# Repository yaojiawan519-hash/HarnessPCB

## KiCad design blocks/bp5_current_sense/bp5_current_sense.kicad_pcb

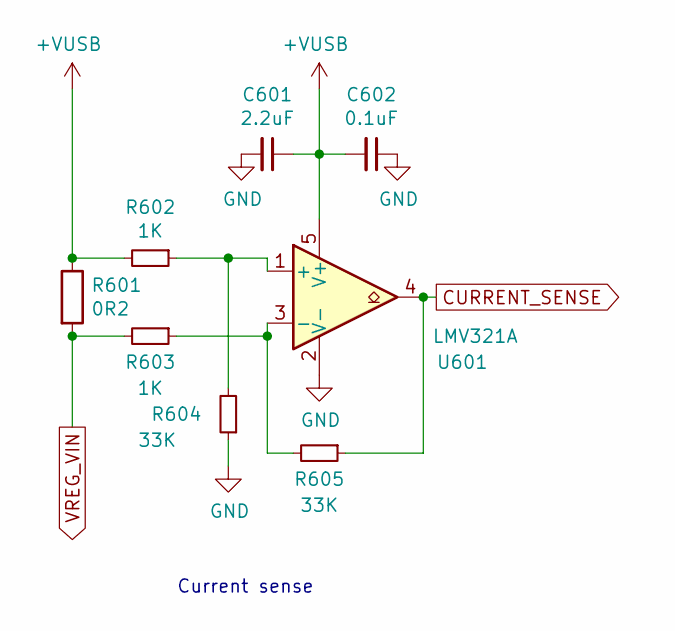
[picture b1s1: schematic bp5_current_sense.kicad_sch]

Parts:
C601: 2.2uF; C_0402_1005Metric
C602: 0.1uF; C_0402_1005Metric
R601: 0R2; R_2512_6332Metric_Pad1.40x3.35mm_HandSolder
R602, R603: 1K; R_0402_1005Metric
R604, R605: 33K; R_0402_1005Metric
U601: LMV321A; SOT-23-5

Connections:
+VUSB: C601.1, C602.2, R601.1, R602.2, U601.5 (V+)
CURRENT_SENSE: R605.1, U601.4
GND: C601.2, C602.1, R604.1, U601.2 (V-)
unnamed: R602.1, R604.2, U601.1 (+)
unnamed: R603.1, R605.2, U601.3 (-)
VREG_VIN: R601.2, R603.2

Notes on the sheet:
Current sense

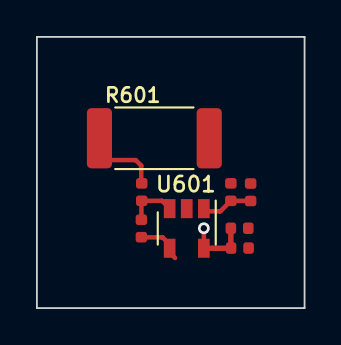
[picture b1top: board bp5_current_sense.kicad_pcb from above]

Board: 4 copper layers, 14.9 x 15.1 mm, 8 parts (0 on the bottom side), 6 nets.

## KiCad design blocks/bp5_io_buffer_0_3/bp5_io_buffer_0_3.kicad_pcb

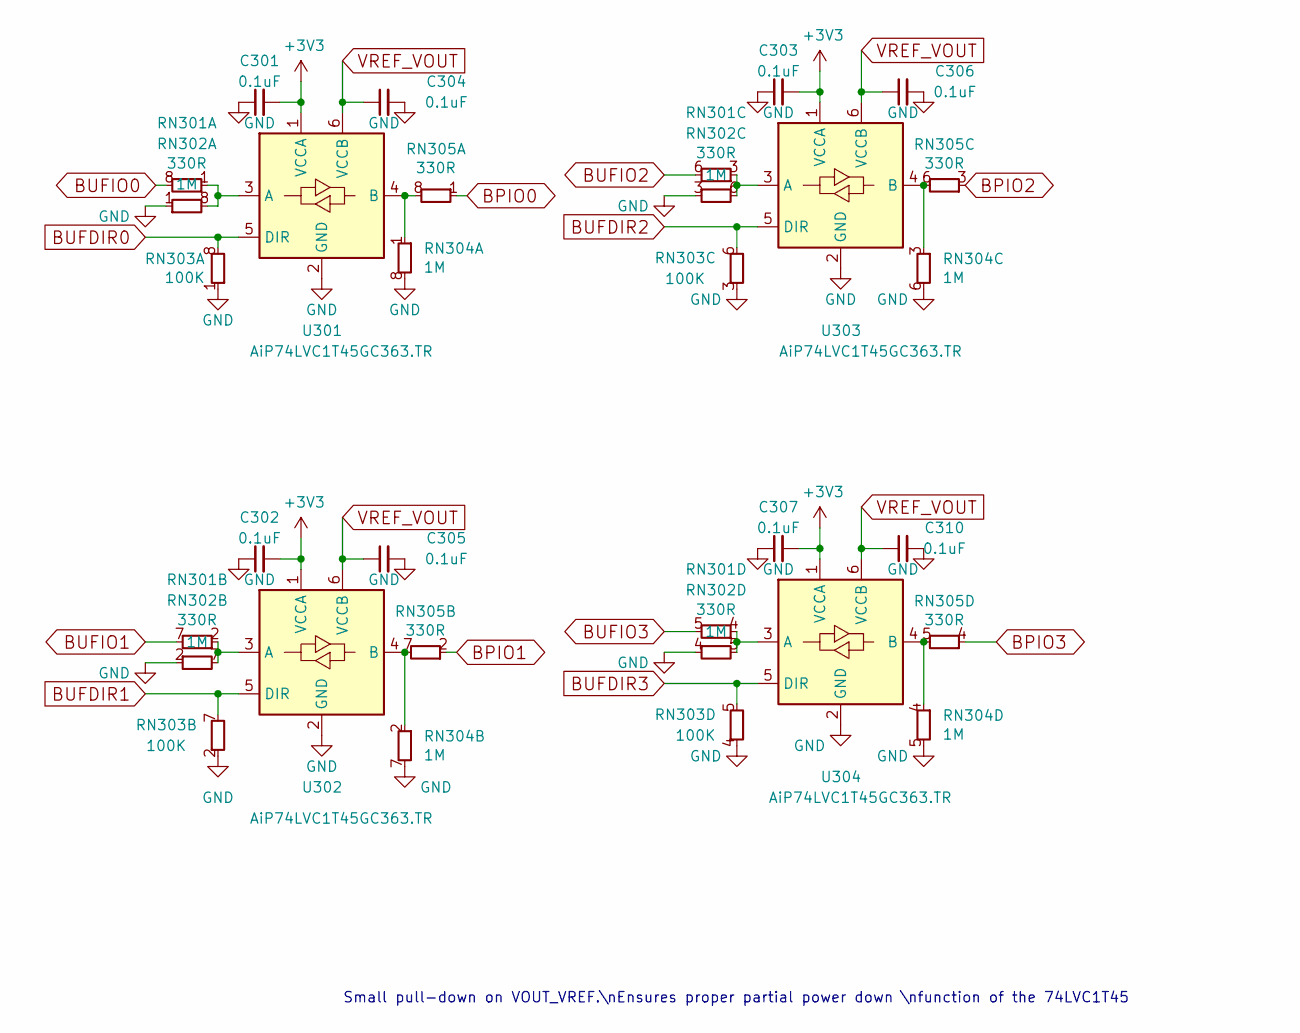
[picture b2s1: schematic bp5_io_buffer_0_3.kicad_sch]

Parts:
C301, C302, C303, C304, C305, C306, C307, C310: 0.1uF; C_0402_1005Metric
RN301, RN305: 330R; R_Array_Convex_4x0402
RN302, RN304: 1M; R_Array_Convex_4x0402
RN303: 100K; R_Array_Convex_4x0402
U301, U302, U303, U304: AiP74LVC1T45GC363.TR; SOT-363_SC-70-6

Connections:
+3V3: C301.2, C302.2, C303.2, C307.2, U301.1 (VCCA), U302.1 (VCCA), U303.1 (VCCA), U304.1 (VCCA)
BPIO0: RN305.1 (R1.1)
BPIO1: RN305.2 (R1.1)
BPIO2: RN305.3 (R1.1)
BPIO3: RN305.4 (R1.1)
BUFDIR0: RN303.8 (R1.8), U301.5 (DIR)
BUFDIR1: RN303.7 (R1.8), U302.5 (DIR)
BUFDIR2: RN303.6 (R1.8), U303.5 (DIR)
BUFDIR3: RN303.5 (R1.8), U304.5 (DIR)
BUFIO0: RN301.8 (R1.8)
BUFIO1: RN301.7 (R1.8)
BUFIO2: RN301.6 (R1.8)
BUFIO3: RN301.5 (R1.8)
GND: C301.1, C302.1, C303.1, C304.2, C305.2, C306.2, C307.1, C310.2, RN302.1 (R1.1), RN302.2 (R1.1), RN302.3 (R1.1), RN302.4 (R1.1), RN303.1 (R1.1), RN303.2 (R1.1), RN303.3 (R1.1), RN303.4 (R1.1), RN304.5 (R1.8), RN304.6 (R1.8), RN304.7 (R1.8), RN304.8 (R1.8), U301.2 (GND), U302.2 (GND), U303.2 (GND), U304.2 (GND)
unnamed: RN301.1 (R1.1), RN302.8 (R1.8), U301.3 (A)
unnamed: RN301.2 (R1.1), RN302.7 (R1.8), U302.3 (A)
unnamed: RN301.3 (R1.1), RN302.6 (R1.8), U303.3 (A)
unnamed: RN301.4 (R1.1), RN302.5 (R1.8), U304.3 (A)
unnamed: RN304.1 (R1.1), RN305.8 (R1.8), U301.4 (B)
unnamed: RN304.2 (R1.1), RN305.7 (R1.8), U302.4 (B)
unnamed: RN304.3 (R1.1), RN305.6 (R1.8), U303.4 (B)
unnamed: RN304.4 (R1.1), RN305.5 (R1.8), U304.4 (B)
VREF_VOUT: C304.1, C305.1, C306.1, C310.1, U301.6 (VCCB), U302.6 (VCCB), U303.6 (VCCB), U304.6 (VCCB)

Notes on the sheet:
Small pull-down on VOUT_VREF.\nEnsures proper partial power down \nfunction of the 74LVC1T45

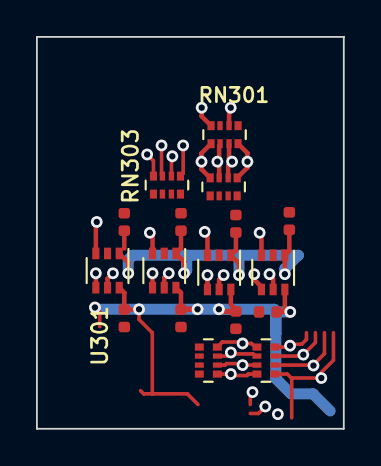
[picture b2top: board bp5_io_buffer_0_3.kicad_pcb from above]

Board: 4 copper layers, 17.1 x 21.8 mm, 17 parts (0 on the bottom side), 15 nets.

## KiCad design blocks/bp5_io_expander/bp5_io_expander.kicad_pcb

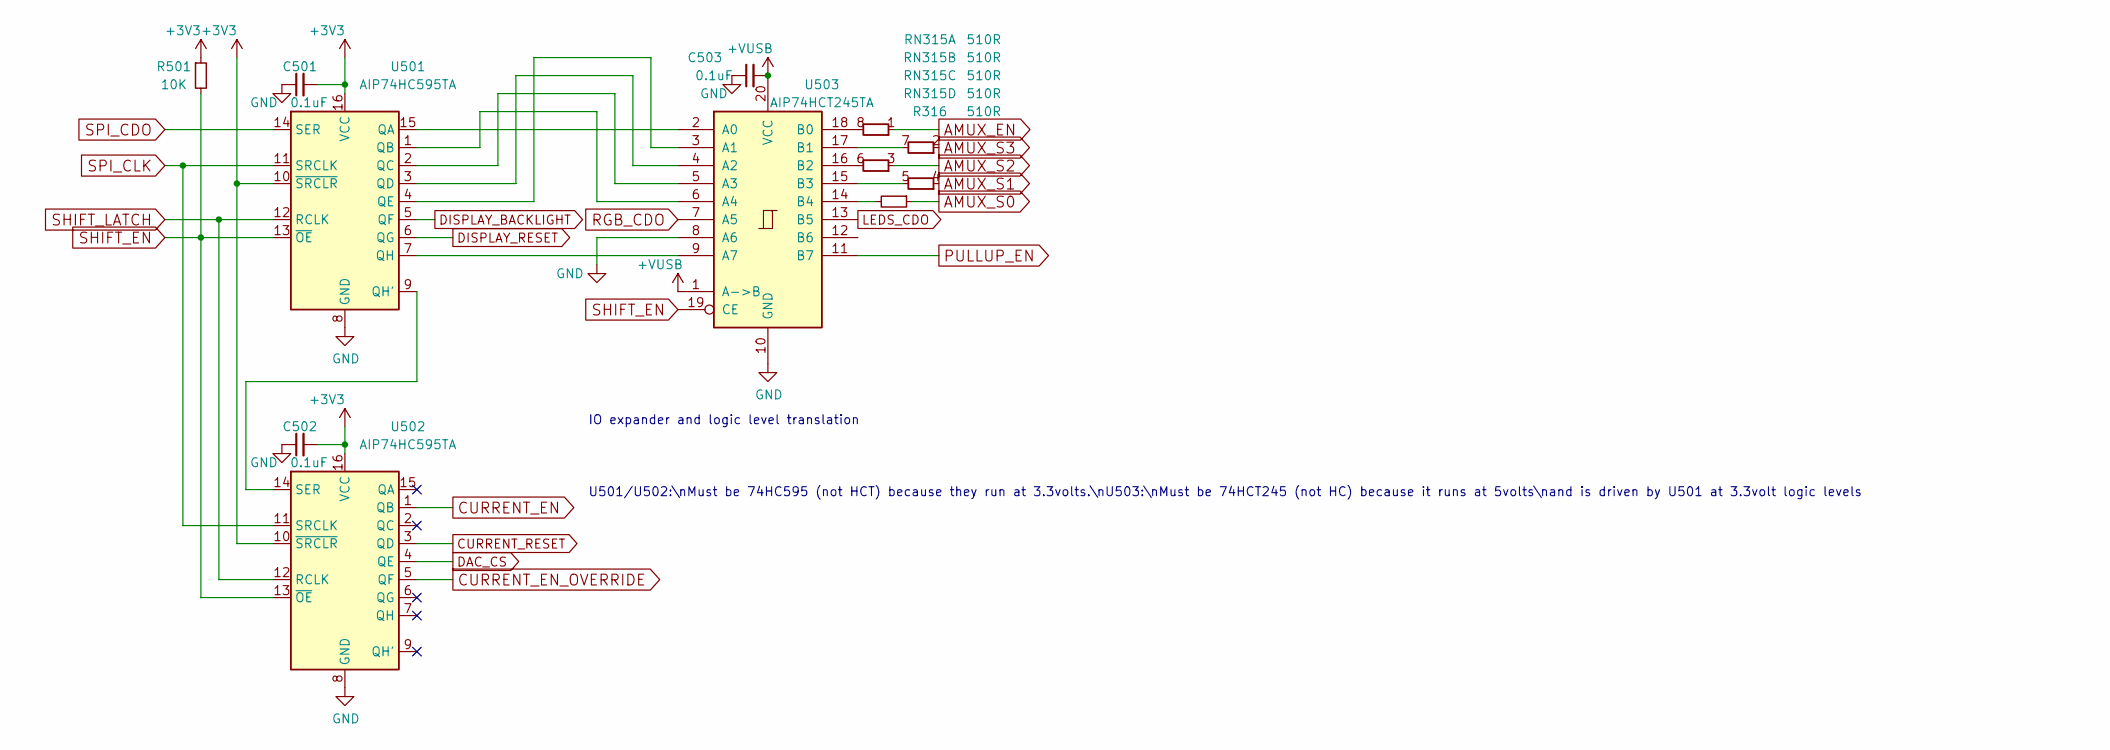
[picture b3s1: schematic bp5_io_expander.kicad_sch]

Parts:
C501, C502, C503: 0.1uF; C_0402_1005Metric
R316: 510R; R_0402_1005Metric
R501: 10K; R_0402_1005Metric
RN315: 510R; R_Array_Convex_4x0402
U501, U502: AIP74HC595TA; TSSOP-16_4.4x5mm_P0.65mm
U503: AIP74HCT245TA; TSSOP-20_4.4x6.5mm_P0.65mm

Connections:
+3V3: C501.2, C502.2, R501.1, U501.10 (~SRCLR), U501.16 (VCC), U502.10 (~SRCLR), U502.16 (VCC)
+VUSB: C503.2, U503.1 (A->B), U503.20 (VCC)
AMUX_EN: RN315.1 (R1.1)
AMUX_S0: R316.1
AMUX_S1: RN315.4 (R1.1)
AMUX_S2: RN315.3 (R1.1)
AMUX_S3: RN315.2 (R1.1)
CURRENT_EN: U502.1 (QB)
CURRENT_EN_OVERRIDE: U502.5 (QF)
CURRENT_RESET: U502.3 (QD)
DAC_CS: U502.4 (QE)
DISPLAY_BACKLIGHT: U501.5 (QF)
DISPLAY_RESET: U501.6 (QG)
GND: C501.1, C502.1, C503.1, U501.8 (GND), U502.8 (GND), U503.8 (A6), U503.10 (GND)
LEDS_CDO: U503.13 (B5)
unnamed: RN315.8 (R1.8), U503.18 (B0)
unnamed: RN315.7 (R1.8), U503.17 (B1)
unnamed: RN315.6 (R1.8), U503.16 (B2)
unnamed: RN315.5 (R1.8), U503.15 (B3)
unnamed: U501.15 (QA), U503.2 (A0)
unnamed: U501.1 (QB), U503.6 (A4)
unnamed: U501.2 (QC), U503.5 (A3)
unnamed: U501.3 (QD), U503.4 (A2)
unnamed: U501.4 (QE), U503.3 (A1)
unnamed: U501.9 (QH'), U502.14 (SER)
unnamed: U501.7 (QH), U503.9 (A7)
unnamed: R316.2, U503.14 (B4)
PULLUP_EN: U503.11 (B7)
RGB_CDO: U503.7 (A5)
SHIFT_EN: R501.2, U501.13 (~OE), U502.13 (~OE), U503.19 (CE)
SHIFT_LATCH: U501.12 (RCLK), U502.12 (RCLK)
SPI_CDO: U501.14 (SER)
SPI_CLK: U501.11 (SRCLK), U502.11 (SRCLK)

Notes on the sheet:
IO expander and logic level translation
U501/U502:\nMust be 74HC595 (not HCT) because they run at 3.3volts.\nU503:\nMust be 74HCT245 (not HC) because it runs at 5volts\nand is driven by U501 at 3.3volt logic levels

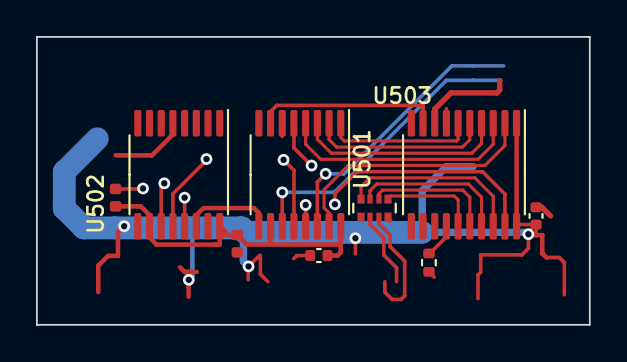
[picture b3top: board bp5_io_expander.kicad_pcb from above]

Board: 4 copper layers, 30.7 x 16.0 mm, 9 parts (0 on the bottom side), 18 nets.

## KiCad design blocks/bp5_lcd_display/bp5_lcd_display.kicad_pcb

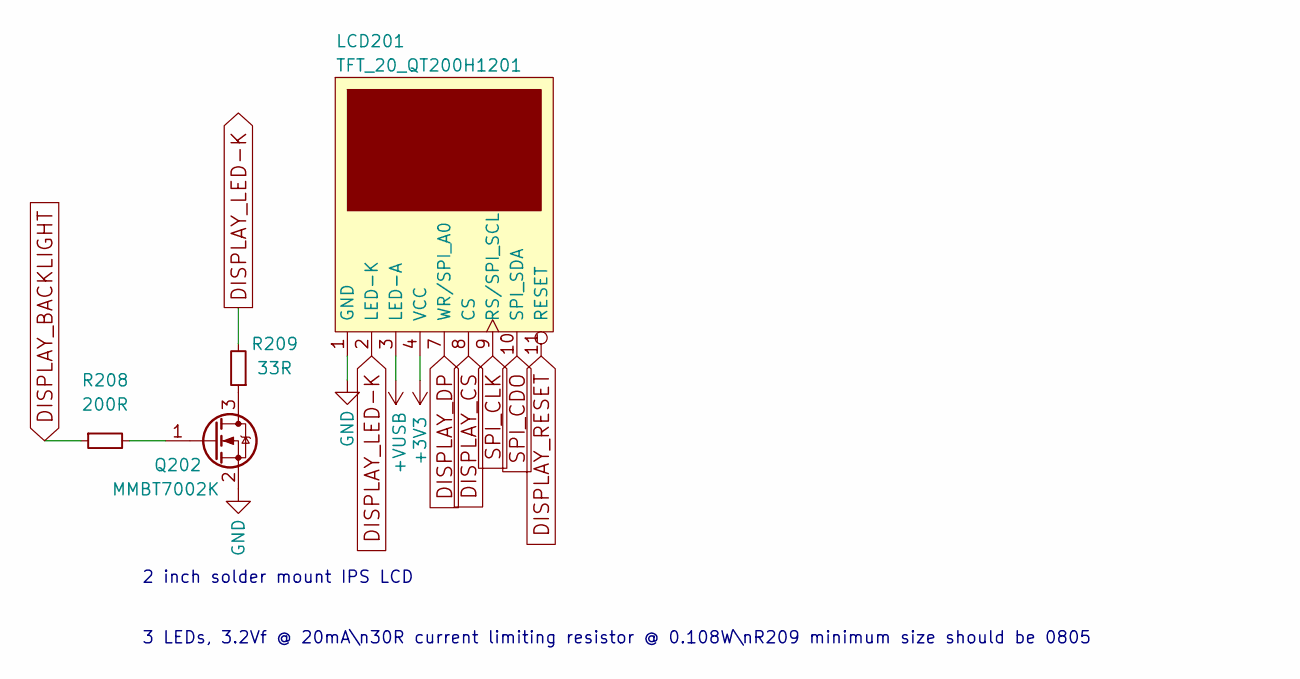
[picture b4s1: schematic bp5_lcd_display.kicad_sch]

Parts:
LCD201: TFT_20_QT200H1201
Q202: MMBT7002K; SOT-23
R208: 200R; R_0402_1005Metric
R209: 33R; R_0805_2012Metric

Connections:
+3V3: LCD201.4 (VCC)
+VUSB: LCD201.3 (LED-A)
DISPLAY_BACKLIGHT: R208.1
DISPLAY_CS: LCD201.8 (CS)
DISPLAY_DP: LCD201.7 (WR/SPI_A0)
DISPLAY_LED-K: LCD201.2 (LED-K), R209.2
DISPLAY_RESET: LCD201.11 (RESET)
GND: LCD201.1 (GND), LCD201.5 (GND), LCD201.6 (GND), LCD201.12 (GND), Q202.2 (S)
unnamed: Q202.3 (D), R209.1
unnamed: Q202.1 (G), R208.2
SPI_CDO: LCD201.10 (SPI_SDA)
SPI_CLK: LCD201.9 (RS/SPI_SCL)

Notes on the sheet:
3 LEDs, 3.2Vf @ 20mA\n30R current limiting resistor @ 0.108W\nR209 minimum size should be 0805
2 inch solder mount IPS LCD

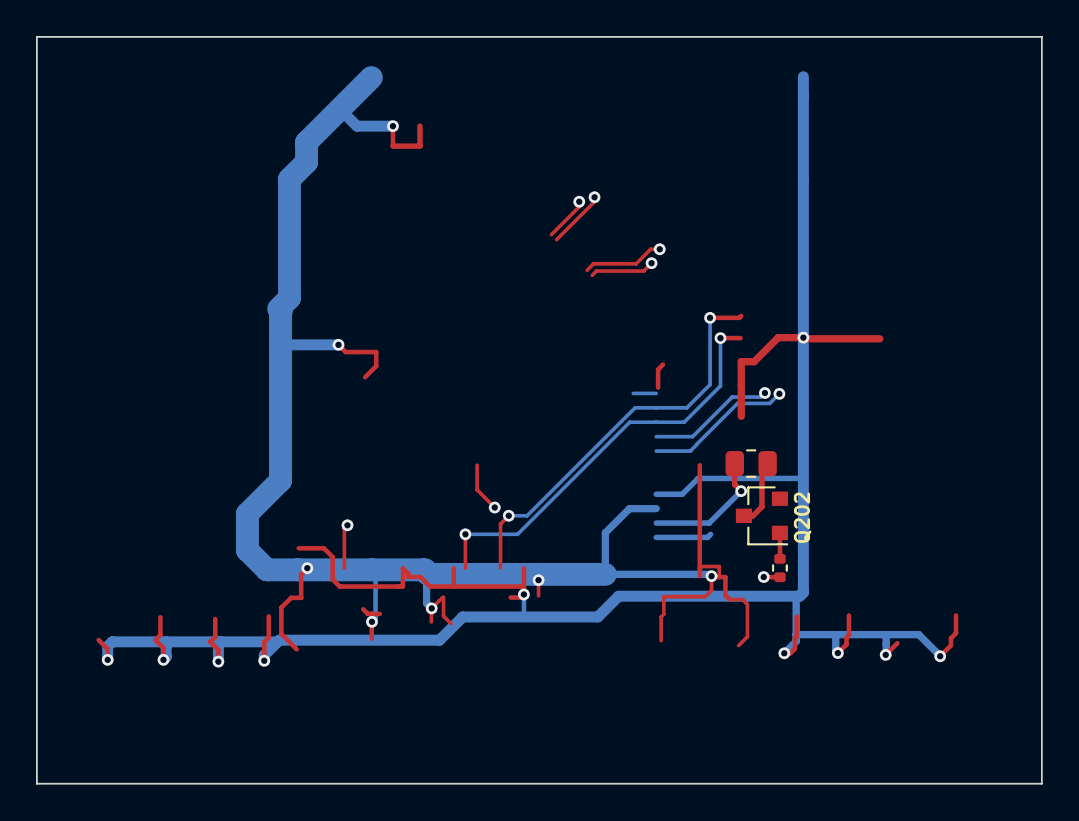
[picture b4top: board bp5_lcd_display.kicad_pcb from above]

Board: 4 copper layers, 55.8 x 41.5 mm, 4 parts (1 on the bottom side), 4 nets.

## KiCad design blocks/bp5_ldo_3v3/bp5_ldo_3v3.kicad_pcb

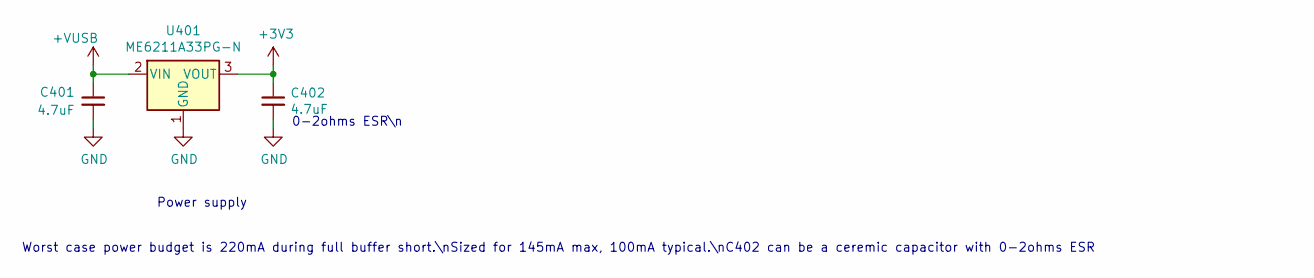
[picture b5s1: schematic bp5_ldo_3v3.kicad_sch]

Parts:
C401, C402: 4.7uF; C_0402_1005Metric
U401: ME6211A33PG-N; SOT-89-3

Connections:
+3V3: C402.1, U401.3 (VOUT)
+VUSB: C401.1, U401.2 (VIN)
GND: C401.2, C402.2, U401.1 (GND)

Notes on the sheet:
Power supply
Worst case power budget is 220mA during full buffer short.\nSized for 145mA max, 100mA typical.\nC402 can be a ceremic capacitor with 0-2ohms ESR
0-2ohms ESR\n

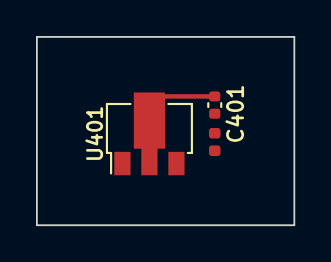
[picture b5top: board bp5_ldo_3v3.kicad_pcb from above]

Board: 4 copper layers, 14.3 x 10.5 mm, 3 parts (0 on the bottom side), 3 nets.

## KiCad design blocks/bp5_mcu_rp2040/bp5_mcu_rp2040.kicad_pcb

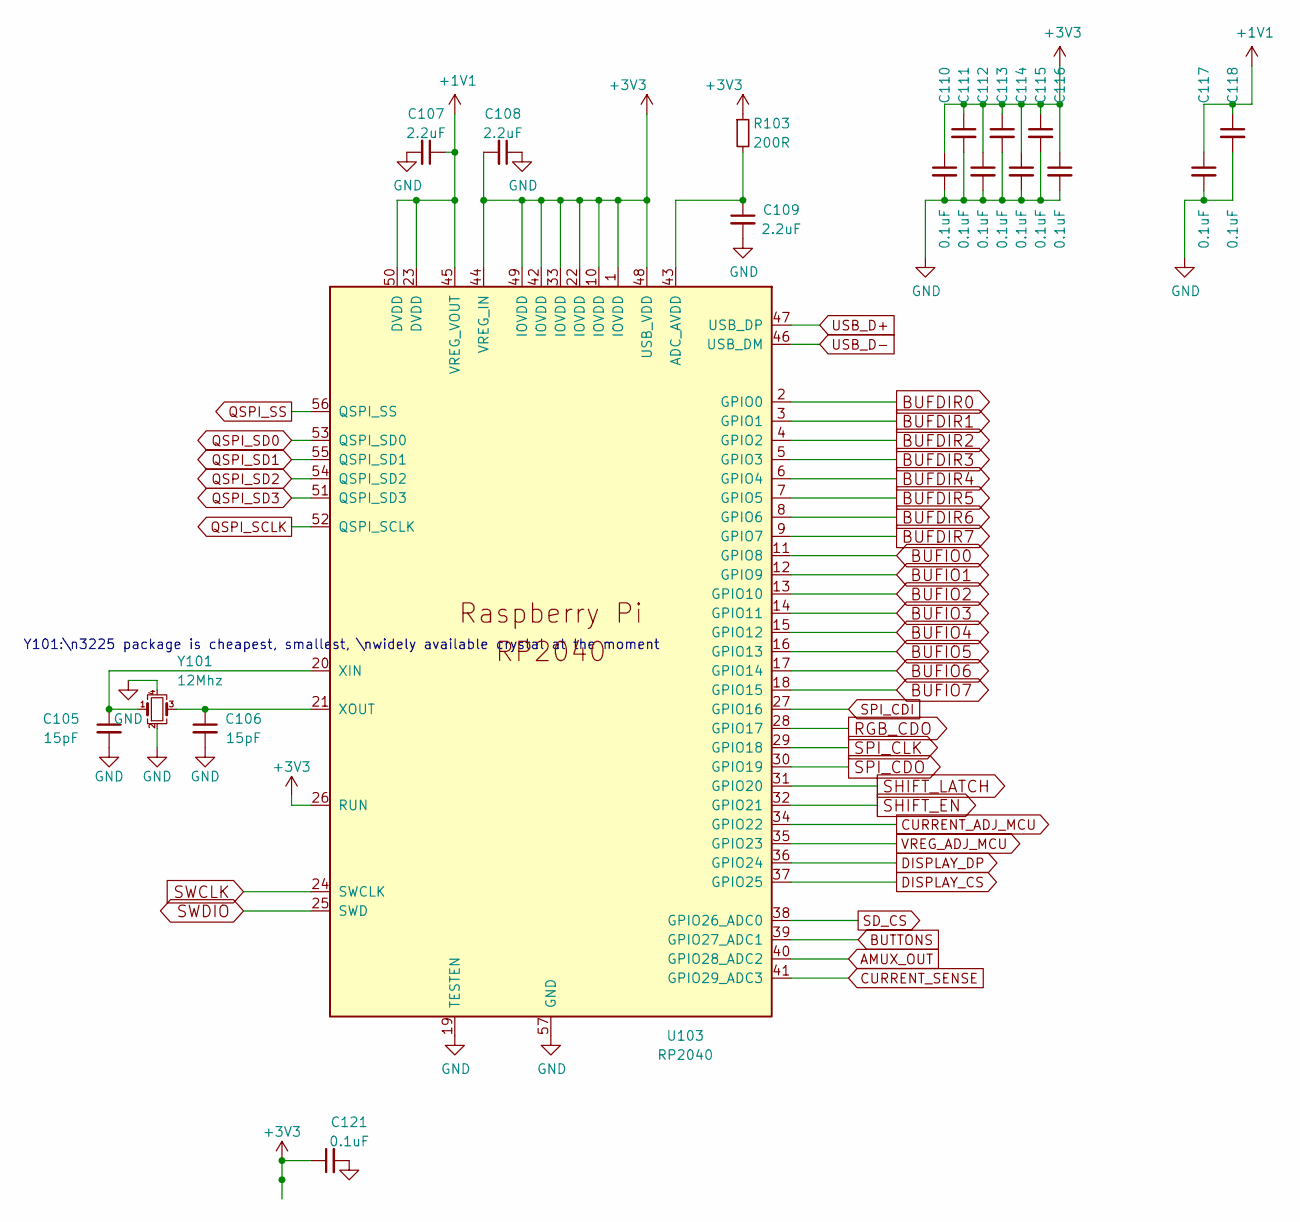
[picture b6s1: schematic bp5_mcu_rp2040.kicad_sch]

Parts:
C105, C106: 15pF; C_0402_1005Metric
C107, C108, C109: 2.2uF; C_0402_1005Metric
C110, C111, C112, C113, C114, C115, C116, C117, C118, C121: 0.1uF; C_0402_1005Metric
R103: 200R; R_0402_1005Metric
U103: RP2040; RP2040-QFN-56
Y101: 12Mhz; Crystal_SMD_3225-4Pin_3.2x2.5mm

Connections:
+1V1: C107.1, C117.1, C118.1, U103.23 (DVDD), U103.45 (VREG_VOUT), U103.50 (DVDD)
+3V3: C108.2, C110.1, C111.1, C112.1, C113.1, C114.1, C115.1, C116.1, C121.1, R103.1, U103.1 (IOVDD), U103.10 (IOVDD), U103.22 (IOVDD), U103.26 (RUN), U103.33 (IOVDD), U103.42 (IOVDD), U103.44 (VREG_IN), U103.48 (USB_VDD), U103.49 (IOVDD)
AMUX_OUT: U103.40 (GPIO28_ADC2)
BUFDIR0: U103.2 (GPIO0)
BUFDIR1: U103.3 (GPIO1)
BUFDIR2: U103.4 (GPIO2)
BUFDIR3: U103.5 (GPIO3)
BUFDIR4: U103.6 (GPIO4)
BUFDIR5: U103.7 (GPIO5)
BUFDIR6: U103.8 (GPIO6)
BUFDIR7: U103.9 (GPIO7)
BUFIO0: U103.11 (GPIO8)
BUFIO1: U103.12 (GPIO9)
BUFIO2: U103.13 (GPIO10)
BUFIO3: U103.14 (GPIO11)
BUFIO4: U103.15 (GPIO12)
BUFIO5: U103.16 (GPIO13)
BUFIO6: U103.17 (GPIO14)
BUFIO7: U103.18 (GPIO15)
BUTTONS: U103.39 (GPIO27_ADC1)
CURRENT_ADJ_MCU: U103.34 (GPIO22)
CURRENT_SENSE: U103.41 (GPIO29_ADC3)
DISPLAY_CS: U103.37 (GPIO25)
DISPLAY_DP: U103.36 (GPIO24)
GND: C105.2, C106.2, C107.2, C108.1, C109.2, C110.2, C111.2, C112.2, C113.2, C114.2, C115.2, C116.2, C117.2, C118.2, C121.2, U103.19 (TESTEN), U103.57 (GND), Y101.2, Y101.4
unnamed: C109.1, R103.2, U103.43 (ADC_AVDD)
unnamed: C105.1, U103.20 (XIN), Y101.1
unnamed: C106.1, U103.21 (XOUT), Y101.3
QSPI_SCLK: U103.52 (QSPI_SCLK)
QSPI_SD0: U103.53 (QSPI_SD0)
QSPI_SD1: U103.55 (QSPI_SD1)
QSPI_SD2: U103.54 (QSPI_SD2)
QSPI_SD3: U103.51 (QSPI_SD3)
QSPI_SS: U103.56 (QSPI_SS)
RGB_CDO: U103.28 (GPIO17)
SD_CS: U103.38 (GPIO26_ADC0)
SHIFT_EN: U103.32 (GPIO21)
SHIFT_LATCH: U103.31 (GPIO20)
SPI_CDI: U103.27 (GPIO16)
SPI_CDO: U103.30 (GPIO19)
SPI_CLK: U103.29 (GPIO18)
SWCLK: U103.24 (SWCLK)
SWDIO: U103.25 (SWD)
USB_D+: U103.47 (USB_DP)
USB_D-: U103.46 (USB_DM)
VREG_ADJ_MCU: U103.35 (GPIO23)

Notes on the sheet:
Y101:\n3225 package is cheapest, smallest, \nwidely available crystal at the moment

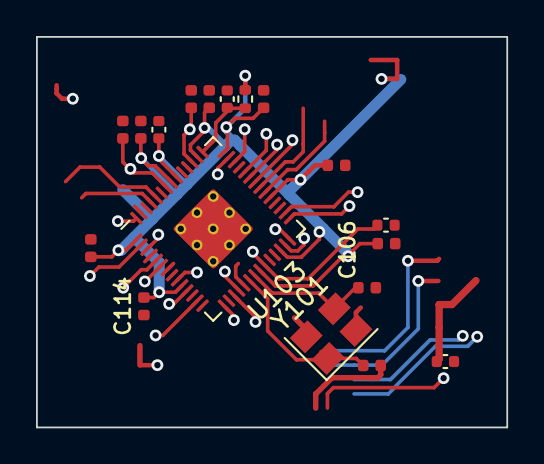
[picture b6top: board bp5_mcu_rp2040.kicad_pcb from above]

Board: 4 copper layers, 26.1 x 21.7 mm, 18 parts (0 on the bottom side), 6 nets.

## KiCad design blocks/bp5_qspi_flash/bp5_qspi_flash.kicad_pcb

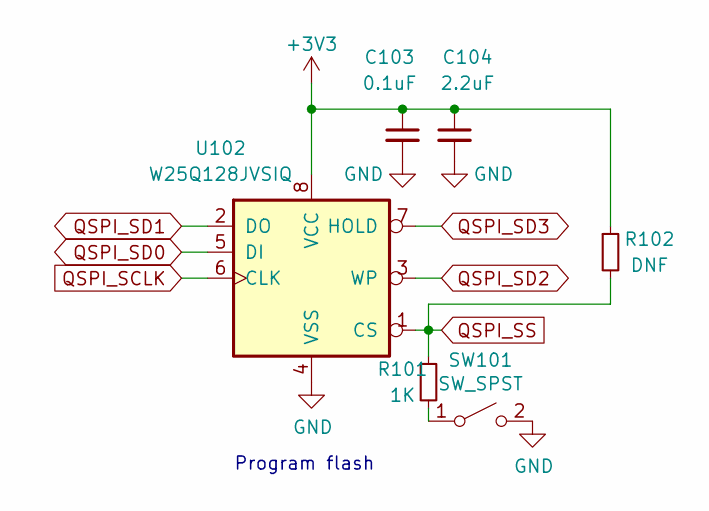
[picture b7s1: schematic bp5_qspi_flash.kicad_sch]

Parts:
C103: 0.1uF; C_0402_1005Metric
C104: 2.2uF; C_0402_1005Metric
R101: 1K; R_0402_1005Metric
R102: DNF; R_0402_1005Metric
SW101: SW_SPST; SW_SPST_PTS810
U102: W25Q128JVSIQ; SOP-8_5.28x5.23mm_P1.27mm

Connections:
+3V3: C103.1, C104.1, R102.1, U102.8 (VCC)
GND: C103.2, C104.2, SW101.2 (B), U102.4 (VSS)
unnamed: R101.2, SW101.1 (A)
QSPI_SCLK: U102.6 (CLK)
QSPI_SD0: U102.5 (DI)
QSPI_SD1: U102.2 (DO)
QSPI_SD2: U102.3 (WP)
QSPI_SD3: U102.7 (HOLD)
QSPI_SS: R101.1, R102.2, U102.1 (CS)

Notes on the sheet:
Program flash

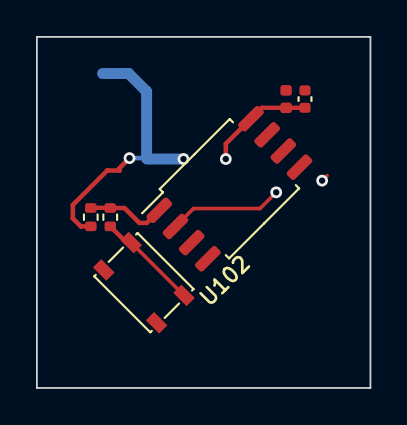
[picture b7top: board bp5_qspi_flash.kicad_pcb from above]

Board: 4 copper layers, 18.5 x 19.5 mm, 6 parts (0 on the bottom side), 4 nets.
